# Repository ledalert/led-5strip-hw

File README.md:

hardware
========

Info

5strip version 0.21 has several silk bugs and one unrouted wire. A revised version will be made soon.

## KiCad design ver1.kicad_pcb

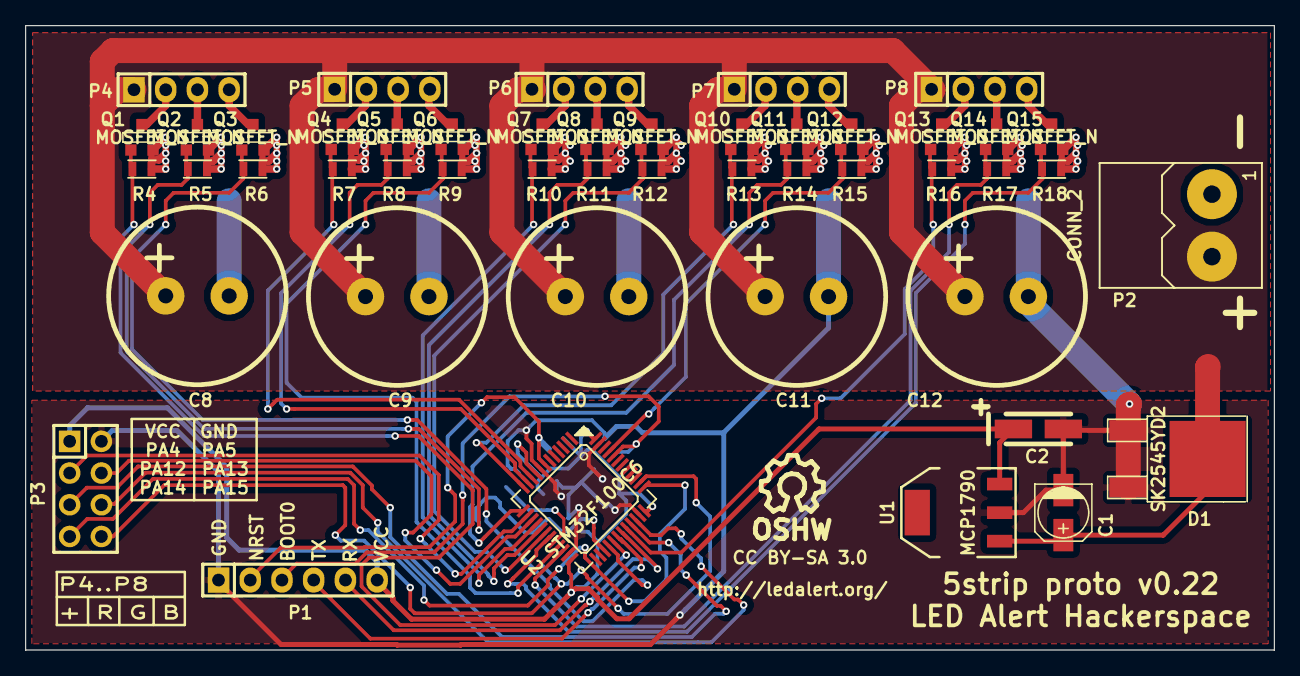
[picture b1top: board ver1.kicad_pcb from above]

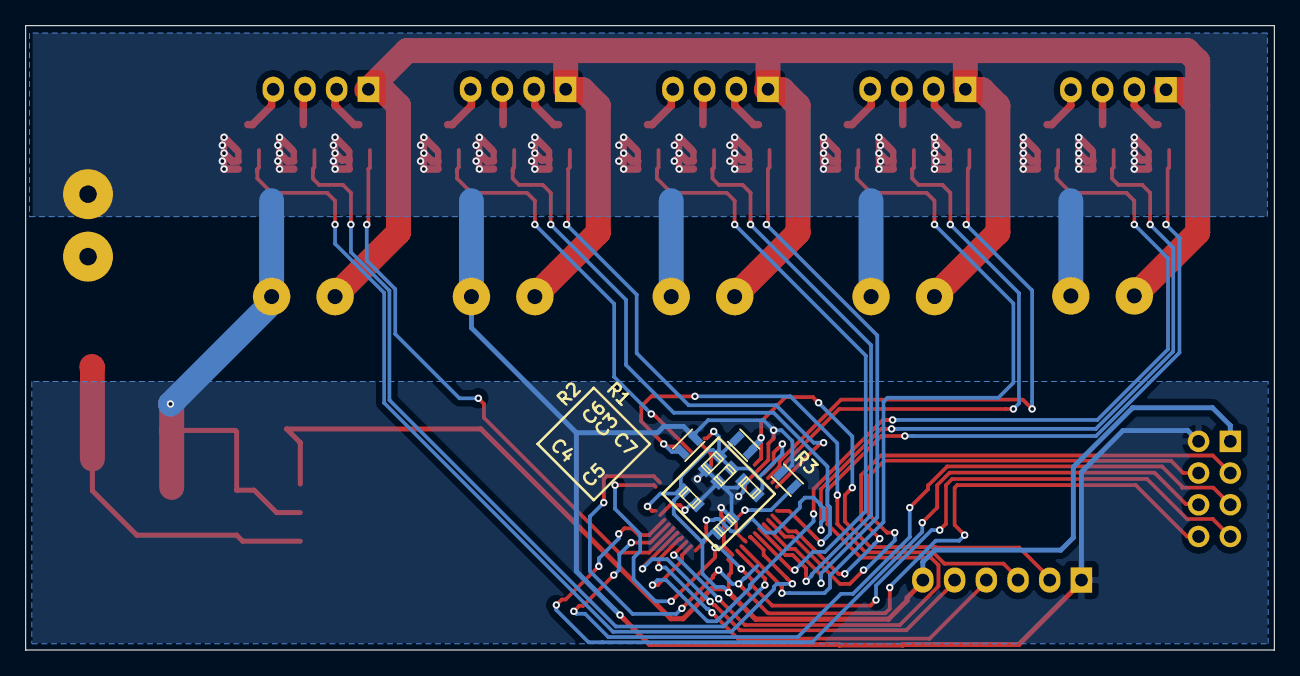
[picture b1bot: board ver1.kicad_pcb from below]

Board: 2 copper layers, 100.0 x 50.0 mm, 57 parts (8 on the bottom side), 44 nets.

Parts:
C1: 1µF 35V; c_elec_4x5.3
C2: 1µF 6.3V; TantalC_SizeA_EIA-3216_HandSoldering
C3: 1µF; c_0603
C4, C5, C6, C7: 100nF; c_0603
C8, C9, C10, C11, C12: CP; Elko_vert_DM14_RM5
D1: SK2545YD2; DPAK-2
P1: CONN_6; Pin_Header_Straight_1x06
P2: CONN_2; terminalblock-2 5mm
P3: CONN_4X2; Pin_Header_Straight_2x04
P4, P5, P6, P7, P8: CONN_4; Pin_Header_Straight_1x04
Q1, Q2, Q3, Q4, Q5, Q6, Q7, Q8, Q9, Q10, Q11, Q12, Q13, Q14, Q15: MOSFET_N; SOT-23-GDS
R1, R2, R3: 10kΩ; R_0603
R4, R5, R6, R7, R8, R9, R10, R11, R12, R13, R14, R15, R16, R17, R18: R; R_0603
SYM: Symbol_OSHW-Logo_SilkScreen_07Jul2012; Symbol_OSHW-Logo_SilkScreen
U1: MCP1790; SOT-223
U2: STM32F100C6; lqfp-48

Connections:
/BOOT0: P1.3, R2.1, U2.44
/BOOT1: R3.1, U2.20
/GPIO1: P3.3, U2.14
/GPIO2: P3.4, U2.15
/GPIO3: P3.5, U2.33
/GPIO4: P3.6, U2.34
/GPIO5: P3.7, U2.37
/GPIO6: P3.8, U2.38
/MCU_RX: P1.5, U2.31
/MCU_TX: P1.4, U2.30
/NRST: P1.2, R1.2, U2.7
/driver1/BE: Q3.G, R6.1, U2.28
/driver1/GE: Q2.G, R5.1, U2.27
/driver1/RE: Q1.G, R4.1, U2.29
/driver2/BE: Q6.G, R9.1, U2.21
/driver2/GE: Q5.G, R8.1, U2.11
/driver2/RE: Q4.G, R7.1, U2.10
/driver3/BE: Q9.G, R12.1, U2.18
/driver3/GE: Q8.G, R11.1, U2.17
/driver3/RE: Q7.G, R10.1, U2.16
/driver4/BE: Q12.G, R15.1, U2.45
/driver4/GE: Q11.G, R14.1, U2.13
/driver4/RE: Q10.G, R13.1, U2.12
/driver5/BE: Q15.G, R18.1, U2.19
/driver5/GE: Q14.G, R17.1, U2.22
/driver5/RE: Q13.G, R16.1, U2.32
GND: C1.2, C2.2, C3.2, C4.2, C5.2, C6.2, C7.2, C8.2, C9.2, C10.2, C11.2, C12.2, D1.1, P1.1, P2.1, P3.2, Q1.S, Q2.S, Q3.S, Q4.S, Q5.S, Q6.S, Q7.S, Q8.S, Q9.S, Q10.S, Q11.S, Q12.S, Q13.S, Q14.S, Q15.S, R2.2, R3.2, R4.2, R5.2, R6.2, R7.2, R8.2, R9.2, R10.2, R11.2, R12.2, R13.2, R14.2, R15.2, R16.2, R17.2, R18.2, U1.2, U2.8, U2.23, U2.35, U2.47
unnamed: P4.2, Q1.D
unnamed: P4.3, Q2.D
unnamed: P4.4, Q3.D
unnamed: P5.2, Q4.D
unnamed: P5.3, Q5.D
unnamed: P5.4, Q6.D
unnamed: P6.2, Q7.D
unnamed: P6.3, Q8.D
unnamed: P6.4, Q9.D
unnamed: P7.2, Q10.D
unnamed: P7.3, Q11.D
unnamed: P7.4, Q12.D
unnamed: P8.2, Q13.D
unnamed: P8.3, Q14.D
unnamed: P8.4, Q15.D
VCC: C2.1, C3.1, C4.1, C5.1, C6.1, C7.1, P1.6, P3.1, R1.1, U1.3, U2.9, U2.24, U2.36, U2.48
VDD: C1.1, C8.1, C9.1, C10.1, C11.1, C12.1, D1.2, P2.2, P4.1, P5.1, P6.1, P7.1, P8.1, U1.1

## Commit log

2015-04-07 Fixed two silk bugs, exported VRML. Bumped version to 0.22
2015-05-14 Restructuring git repos

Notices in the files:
ver1.kicad_pcb:
CC BY-SA 3.0
